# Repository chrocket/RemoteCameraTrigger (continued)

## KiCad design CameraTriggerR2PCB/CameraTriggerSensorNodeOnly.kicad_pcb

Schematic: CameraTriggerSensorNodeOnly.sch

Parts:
BZ1: Buzzer; Buzzer_TDK_PS1240P02BT_D12.2mm_H6.5mm
C1: 25uf; CP_Radial_Tantal_D5.0mm_P5.00mm
C2: 0.1uf; CP_Radial_Tantal_D5.0mm_P5.00mm
C3, C4, C5, C6: 0.01 μF; C_Disc_D7.5mm_W2.5mm_P5.00mm
D1: LED Arm; LED_D3.0mm
D2: LED Trig; LED_D3.0mm
D3: D; D_DO-201AD_P12.70mm_Horizontal
D4: PWR; LED_D3.0mm
GND1: TestPoint; TestPoint_Keystone_5000-5004_Miniature
H1, H2, H3, H4: MountingHole_3.7mm_Pad
IC1: 3178; Mouser2 Part Number 485-3178
J1: Power; AMASS_XT30U-F_1x02_P5.0mm_Vertical
J2: Qwiic_Connector; 1X04_1MM_RA_STRESSRELIEF
J3: Aux out; TerminalBlock_TE_282834-2_1x02_P2.54mm_Horizontal
J4: HighLowIn; TerminalBlock_TE_282834-3_1x03_P2.54mm_Horizontal
J5: Laser; TerminalBlock_TE_282834-2_1x02_P2.54mm_Horizontal
J6: Sensor; TerminalBlock_TE_282834-3_1x03_P2.54mm_Horizontal
J7: XLR5; Jack_XLR_Neutrik_NC5MBH_Horizontal
J13: Serial; TerminalBlock_TE_282834-4_1x04_P2.54mm_Horizontal
J14: Ext power switch; TerminalBlock_TE_282834-2_1x02_P2.54mm_Horizontal
Q1: PN2222A; TO-92L_HandSolder
Q2: KSC1815YTA; TO-92L_Inline_Wide
R1, R2, R5, R6: 1K; R_Axial_DIN0207_L6.3mm_D2.5mm_P7.62mm_Horizontal
R3: 5K; R_Axial_DIN0207_L6.3mm_D2.5mm_P7.62mm_Horizontal
R4: 220; R_Axial_DIN0207_L6.3mm_D2.5mm_P7.62mm_Horizontal
R8: 15K; R_Axial_DIN0207_L6.3mm_D2.5mm_P7.62mm_Horizontal
RV1: 1K; Potentiometer_Alps_RK09K_Single_Vertical
SW1: AS11CB; Manufacturer_Part_Number AS11CB; Mouser Part Number 633-AS11CB
SW2: SW_Arm; KSA_Tactile_SPST
SW3: SW_Poll; KSA_Tactile_SPST
SW4: SW_SPDT; SW_Slide_1P2T_CK_OS102011MS2Q
TP1: Gnd; TestPoint_Keystone_5000-5004_Miniature
TP1+5: +5V; TestPoint_Keystone_5010-5014_Multipurpose
TP2+3.3V1: +3.3V; TestPoint_Keystone_5010-5014_Multipurpose
TP3Arm1: Arm; TestPoint_Keystone_5010-5014_Multipurpose
TP4Fire1: Fire; TestPoint_Keystone_5010-5014_Multipurpose
TP7Poll1: Poll; TestPoint_Keystone_5010-5014_Multipurpose
TP8: HighLowIn; TestPoint_Keystone_5010-5014_Multipurpose
TP9: LowHighIn; TestPoint_Keystone_5010-5014_Multipurpose
U1: LM7805_TO220; TO-220-3_Vertical

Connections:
+3V3: BZ1.1 (-), C4.1, IC1.27, J2.2, J4.3, J6.1, J7.3, R6.1, RV1.1, TP2+3.3V1.1
+5V: C2.1, C3.1, IC1.3, J5.1, J7.1, J13.1, R4.1, TP1+5.1, U1.3 (VO); also elsewhere on the board
+7.5V: J1.2, J14.2, SW1.1
/13: IC1.4
/A0: IC1.24
/A4: IC1.20
/AREF: IC1.26
/EN: IC1.2
/FREE: IC1.13
/MISO: IC1.16
/MOSI: IC1.17
/SCK: IC1.18
/VBAT: IC1.1
/~RST: IC1.28
ArmIn: IC1.23, SW2.2
ArmInd: IC1.9, R1.2, TP3Arm1.1
AuxIn: C5.1, IC1.21, J4.2, SW4.1, TP8.1
AuxOut: IC1.8, R3.2
Buzzer: IC1.7, R2.2
GND: C1.2, C2.2, C3.2, C4.2, C5.2, C6.2, D4.1 (K), GND1.1, H1.1, H2.1, H3.1, H4.1, IC1.25, J1.1, J2.1, J3.2, J4.1, J6.3, J7.5, J13.4, Q1.1 (E), Q2.1, R5.1, R8.2, RV1.3, SW2.1, SW3.1, TP1.1, U1.2 (GND); also elsewhere on the board
Laser: J5.2, J7.2, Q1.3 (C)
unnamed: BZ1.2 (+), Q2.2, R6.2
unnamed: C1.1, D3.1 (K), U1.1 (VI)
unnamed: D1.1 (K), Q1.2 (B)
unnamed: D1.2 (A), R1.1
unnamed: D2.1 (K), R5.2
unnamed: D3.2 (A), J14.1, SW1.3
unnamed: D4.2 (A), R4.2
unnamed: J3.1, R3.1
unnamed: J7.4, SW4.2
unnamed: Q2.3, R2.1
Poll: IC1.22, SW3.2, TP7Poll1.1
Rx_serial: IC1.15, J13.2
SCL_qwiic: IC1.11, J2.4
SDA_qwiic: IC1.12, J2.3
SensorIn: C6.1, IC1.10, J6.2, R8.1, SW4.3, TP9.1
Shutter: D2.2 (A), IC1.5, TP4Fire1.1
Threshold: IC1.19, RV1.2
Tx_serial: IC1.14, J13.3

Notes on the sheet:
+3v
GND
+3.3V
RocketTrig Curtis Heisey

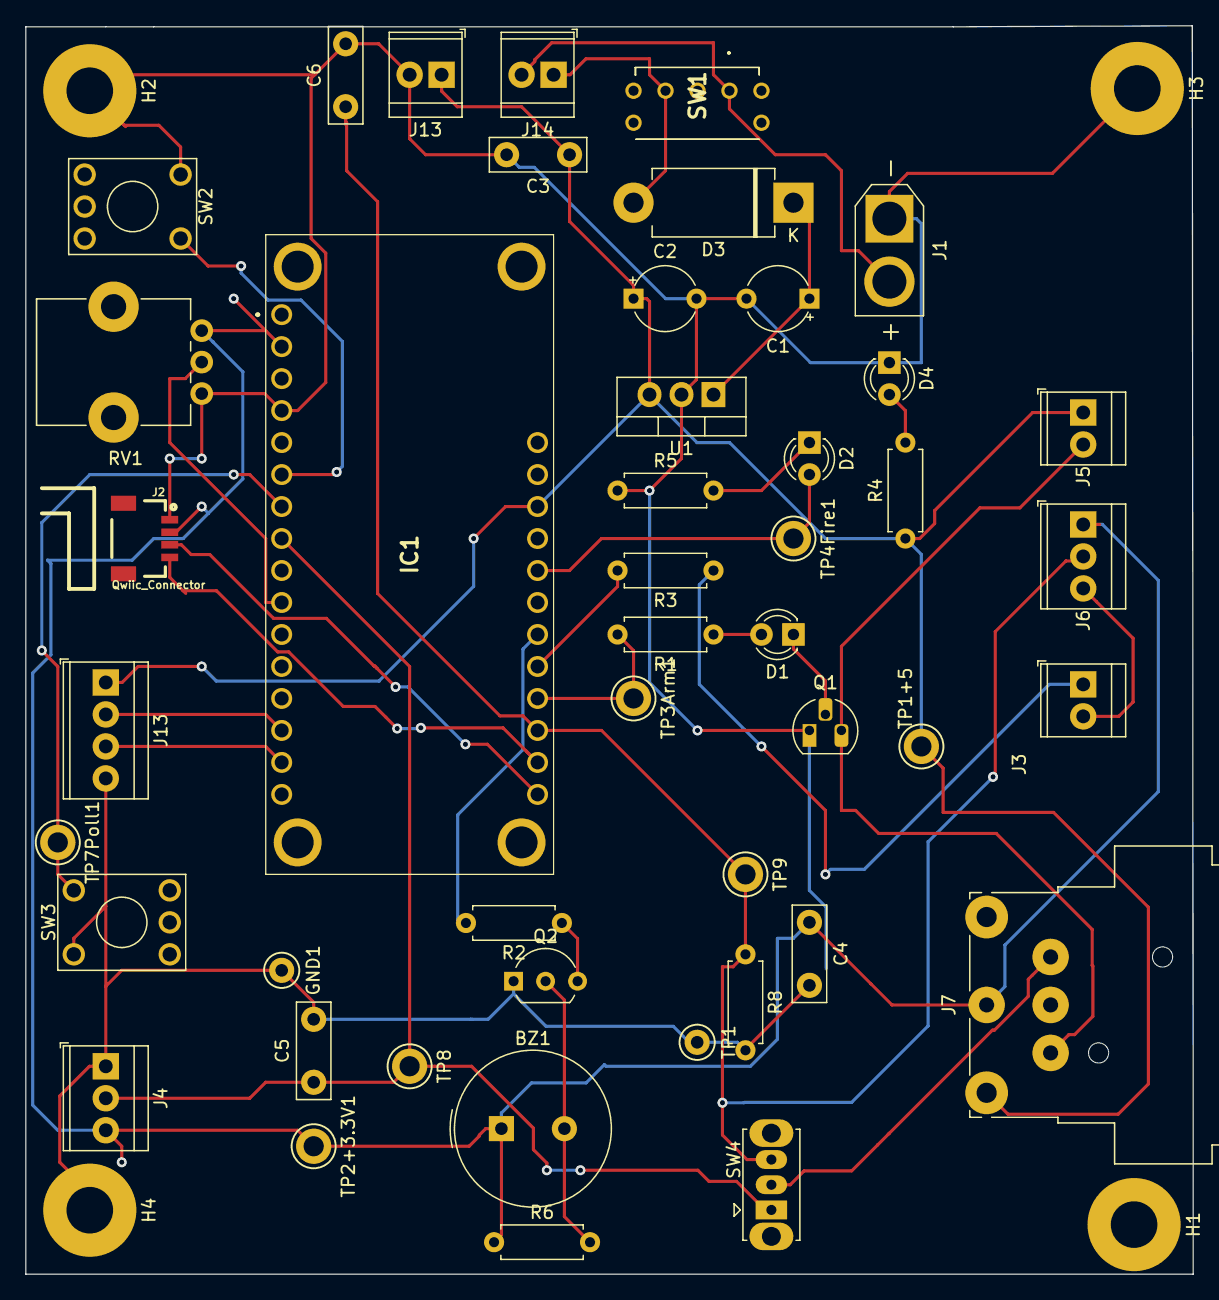
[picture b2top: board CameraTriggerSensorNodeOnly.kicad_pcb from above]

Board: 2 copper layers, 92.7 x 99.1 mm, 50 parts (0 on the bottom side), 28 nets.

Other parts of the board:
J13#2: +5V Always on; TerminalBlock_TE_282834-2_1x02_P2.54mm_Horizontal

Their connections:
+5V: J13#2.1; also elsewhere on the board
GND: J13#2.2; also elsewhere on the board

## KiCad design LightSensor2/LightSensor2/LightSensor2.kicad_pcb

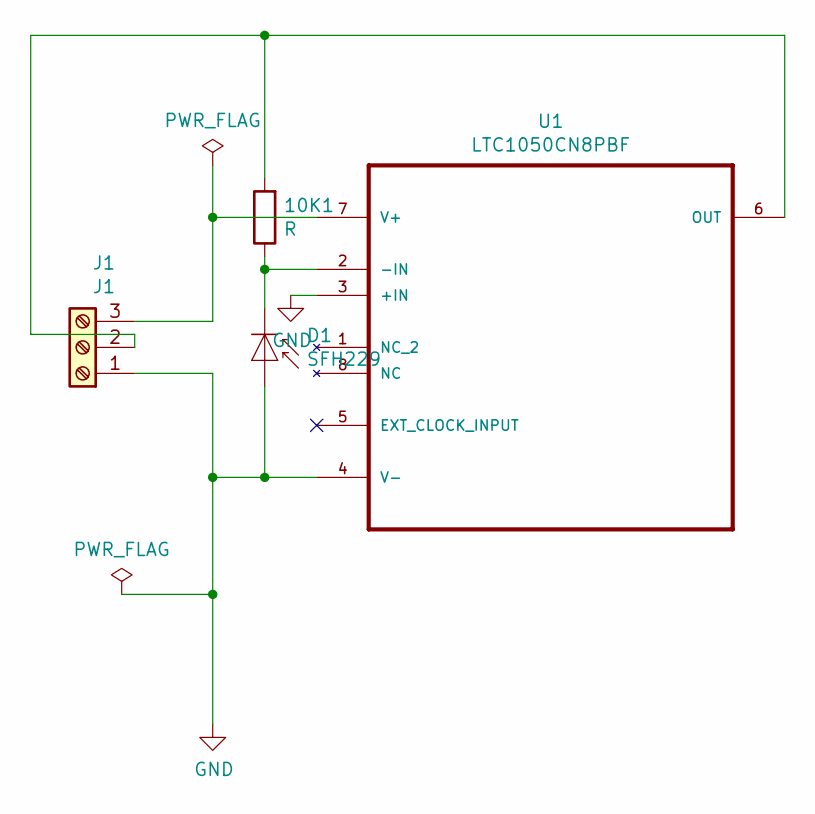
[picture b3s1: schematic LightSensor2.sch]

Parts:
10K1: R; R_Axial_DIN0207_L6.3mm_D2.5mm_P10.16mm_Horizontal
D1: SFH229; LED_D5.0mm_IRGrey
J1: J1; TerminalBlock_TE_282834-3_1x03_P2.54mm_Horizontal
U1: LTC1050CN8PBF; DIP-8_W7.62mm_LongPads

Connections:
GND: D1.2 (A), J1.1, U1.3 (+IN), U1.4 (V-)
unnamed: 10K1.1, D1.1 (K), U1.2 (-IN)
unnamed: 10K1.2, J1.2, U1.6 (OUT)
unnamed: J1.3, U1.7 (V+)

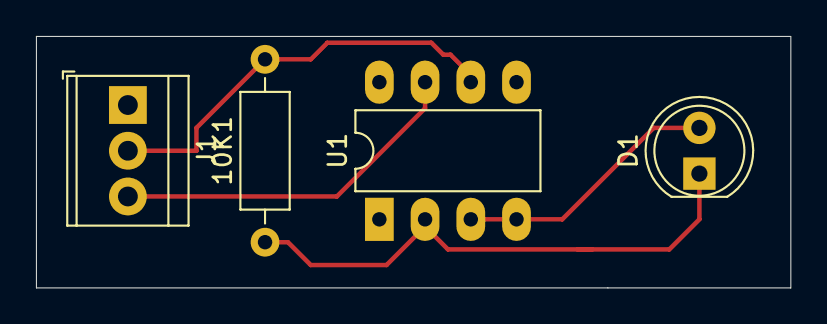
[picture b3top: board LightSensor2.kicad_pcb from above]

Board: 2 copper layers, 41.9 x 14.0 mm, 4 parts (0 on the bottom side), 4 nets.

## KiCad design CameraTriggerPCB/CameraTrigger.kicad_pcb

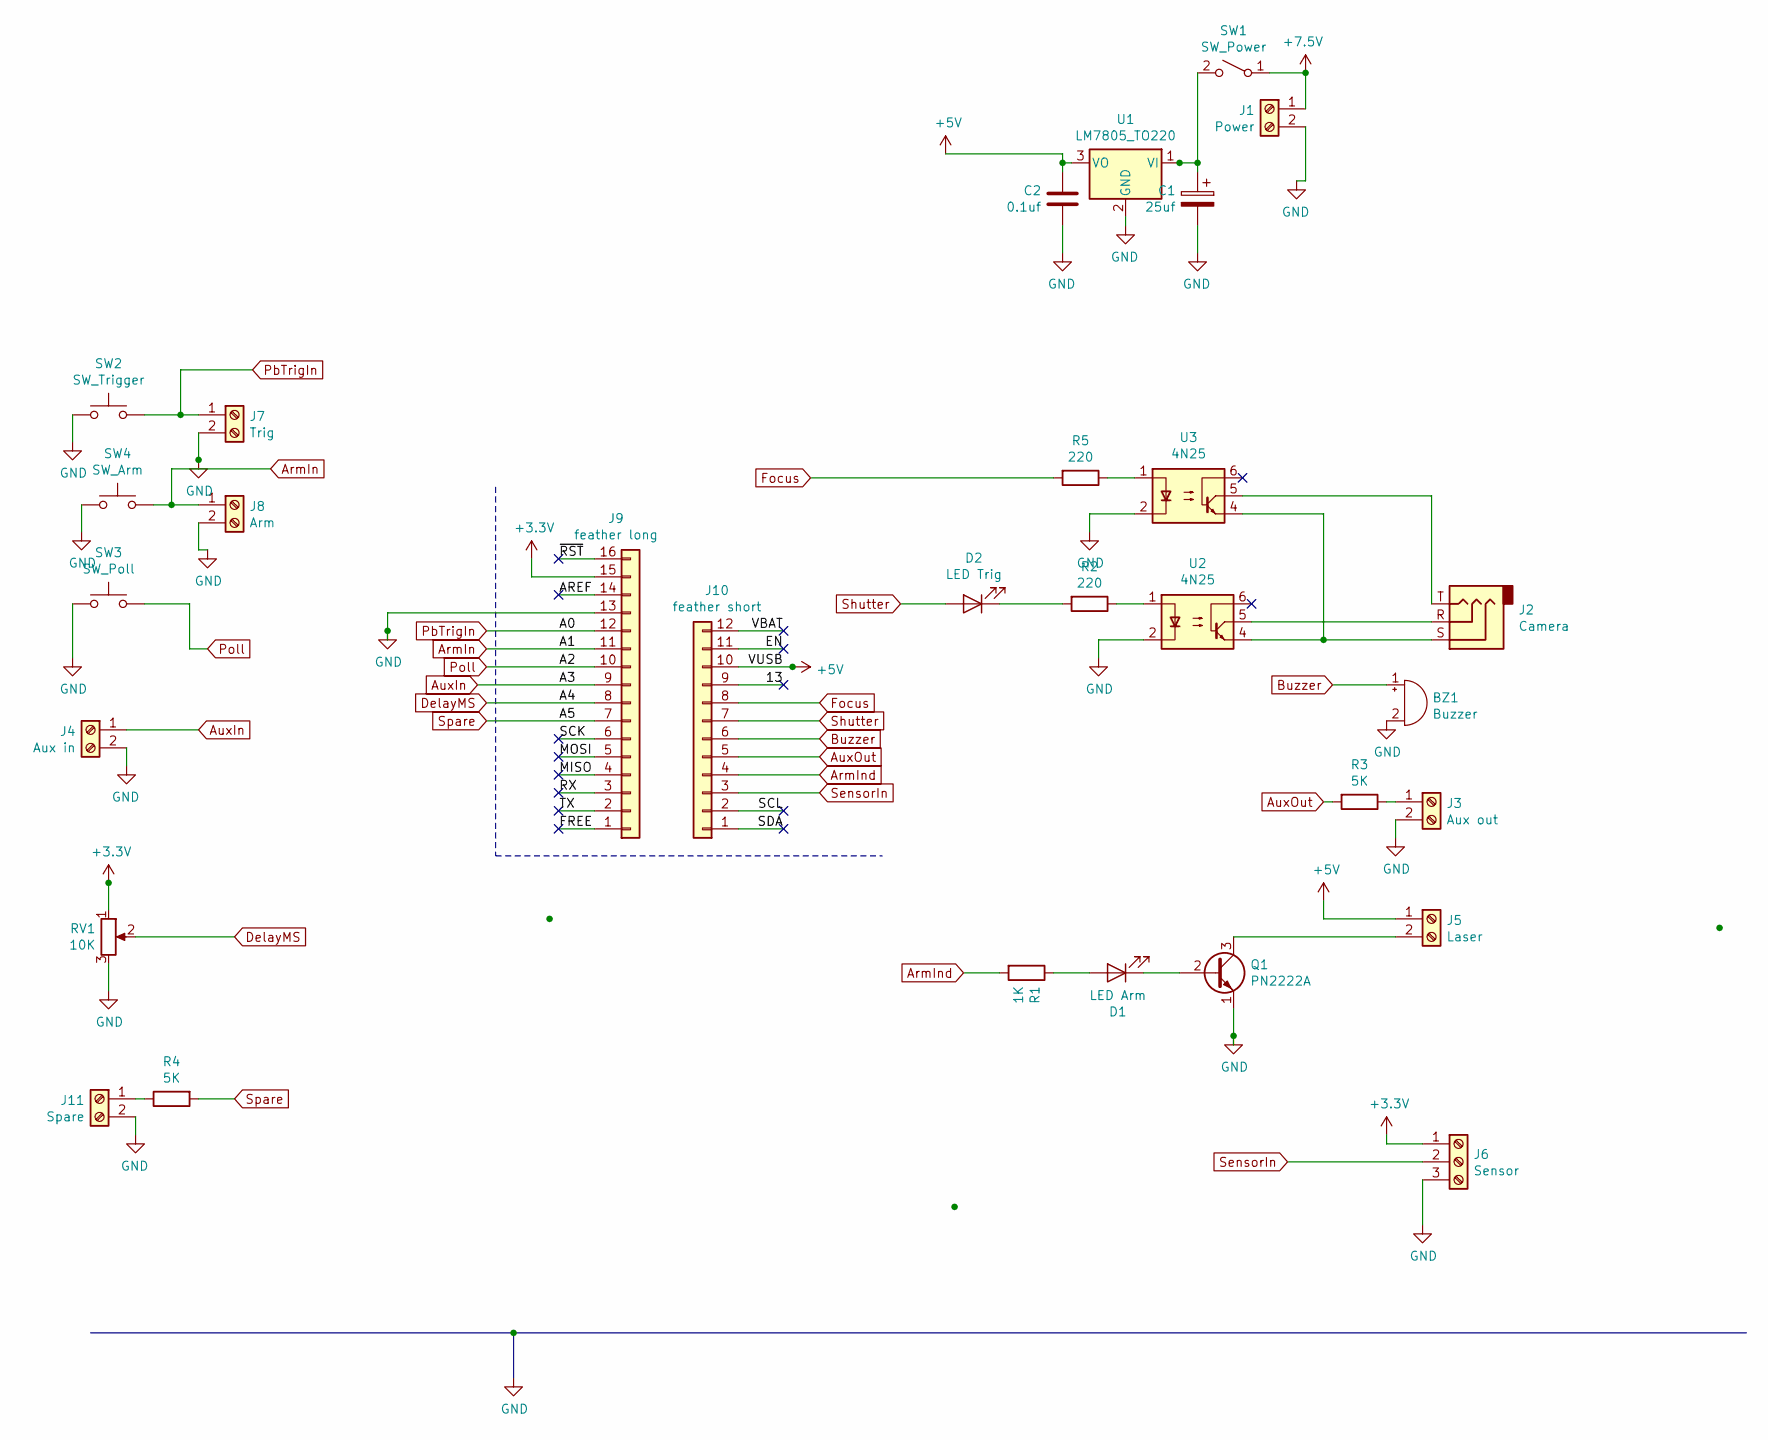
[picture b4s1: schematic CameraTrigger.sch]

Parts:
BZ1: Buzzer; Buzzer_TDK_PS1240P02BT_D12.2mm_H6.5mm
C1: 25uf; CP_Radial_Tantal_D5.0mm_P5.00mm
C2: 0.1uf; CP_Radial_Tantal_D5.0mm_P5.00mm
D1: LED Arm; LED_D2.0mm_W4.8mm_H2.5mm_FlatTop
D2: LED Trig; LED_D2.0mm_W4.8mm_H2.5mm_FlatTop
J1: Power; TerminalBlock_TE_282834-2_1x02_P2.54mm_Horizontal
J2: Camera; Jack_3.5mm_CUI_SJ1-3533NG_Horizontal_CircularHoles
J3: Aux out; TerminalBlock_TE_282834-2_1x02_P2.54mm_Horizontal
J4: Aux in; TerminalBlock_TE_282834-2_1x02_P2.54mm_Horizontal
J5: Laser; TerminalBlock_TE_282834-2_1x02_P2.54mm_Horizontal
J6: Sensor; TerminalBlock_TE_282834-3_1x03_P2.54mm_Horizontal
J7: Trig; TerminalBlock_TE_282834-2_1x02_P2.54mm_Horizontal
J8: Arm; TerminalBlock_TE_282834-2_1x02_P2.54mm_Horizontal
J9: feather long; PinHeader_1x16_P2.54mm_Vertical
J10: feather short; PinHeader_1x12_P2.54mm_Vertical
J11: Spare; TerminalBlock_TE_282834-2_1x02_P2.54mm_Horizontal
Q1: PN2222A; TO-92_Inline
R1: 1K; R_Axial_DIN0207_L6.3mm_D2.5mm_P7.62mm_Horizontal
R2, R5: 220; R_Axial_DIN0207_L6.3mm_D2.5mm_P7.62mm_Horizontal
R3, R4: 5K; R_Axial_DIN0207_L6.3mm_D2.5mm_P7.62mm_Horizontal
RV1: 10K; Potentiometer_Alps_RK09K_Single_Vertical
SW1: SW_Power; SW_DIP_SPSTx01_Slide_9.78x4.72mm_W7.62mm_P2.54mm
SW2: SW_Trigger; KSA_Tactile_SPST
SW3: SW_Poll; KSA_Tactile_SPST
SW4: SW_Arm; KSA_Tactile_SPST
U1: LM7805_TO220; TO-220-3_Vertical
U2, U3: 4N25; DIP-6_W7.62mm

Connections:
+3V3: J6.1, J9.15, RV1.1
+5V: C2.1, J5.1, J10.10, U1.3 (VO)
+7.5V: J1.1, SW1.1 (A)
/13: J10.9
/AREF: J9.14
/EN: J10.11
/FREE: J9.1
/MISO: J9.4
/MOSI: J9.5
/RX: J9.3
/SCK: J9.6
/SCL: J10.2
/SDA: J10.1
/TX: J9.2
/VBAT: J10.12
/~RST: J9.16
ArmIn: J8.1, J9.11, SW4.2
ArmInd: J10.4, R1.2
AuxIn: J4.1, J9.9
AuxOut: J10.5, R3.2
Buzzer: BZ1.1 (-), J10.6
DelayMS: J9.8, RV1.2
Focus: J10.8, R5.2
GND: BZ1.2 (+), C1.2, C2.2, J1.2, J3.2, J4.2, J6.3, J7.2, J8.2, J9.13, J11.2, Q1.1 (E), RV1.3, SW2.1, SW3.1, SW4.1, U1.2 (GND), U2.2, U3.2
unnamed: C1.1, SW1.2 (B), U1.1 (VI)
unnamed: D1.1 (K), Q1.2 (B)
unnamed: D1.2 (A), R1.1
unnamed: D2.1 (K), R2.2
unnamed: J2.R, U2.5
unnamed: J2.S, U2.4, U3.4
unnamed: J2.T, U3.5
unnamed: J3.1, R3.1
unnamed: J5.2, Q1.3 (C)
unnamed: J11.1, R4.1
unnamed: R2.1, U2.1
unnamed: R5.1, U3.1
PbTrigIn: J7.1, J9.12, SW2.2
Poll: J9.10, SW3.2
SensorIn: J6.2, J10.3
Shutter: D2.2 (A), J10.7
Spare: J9.7, R4.2

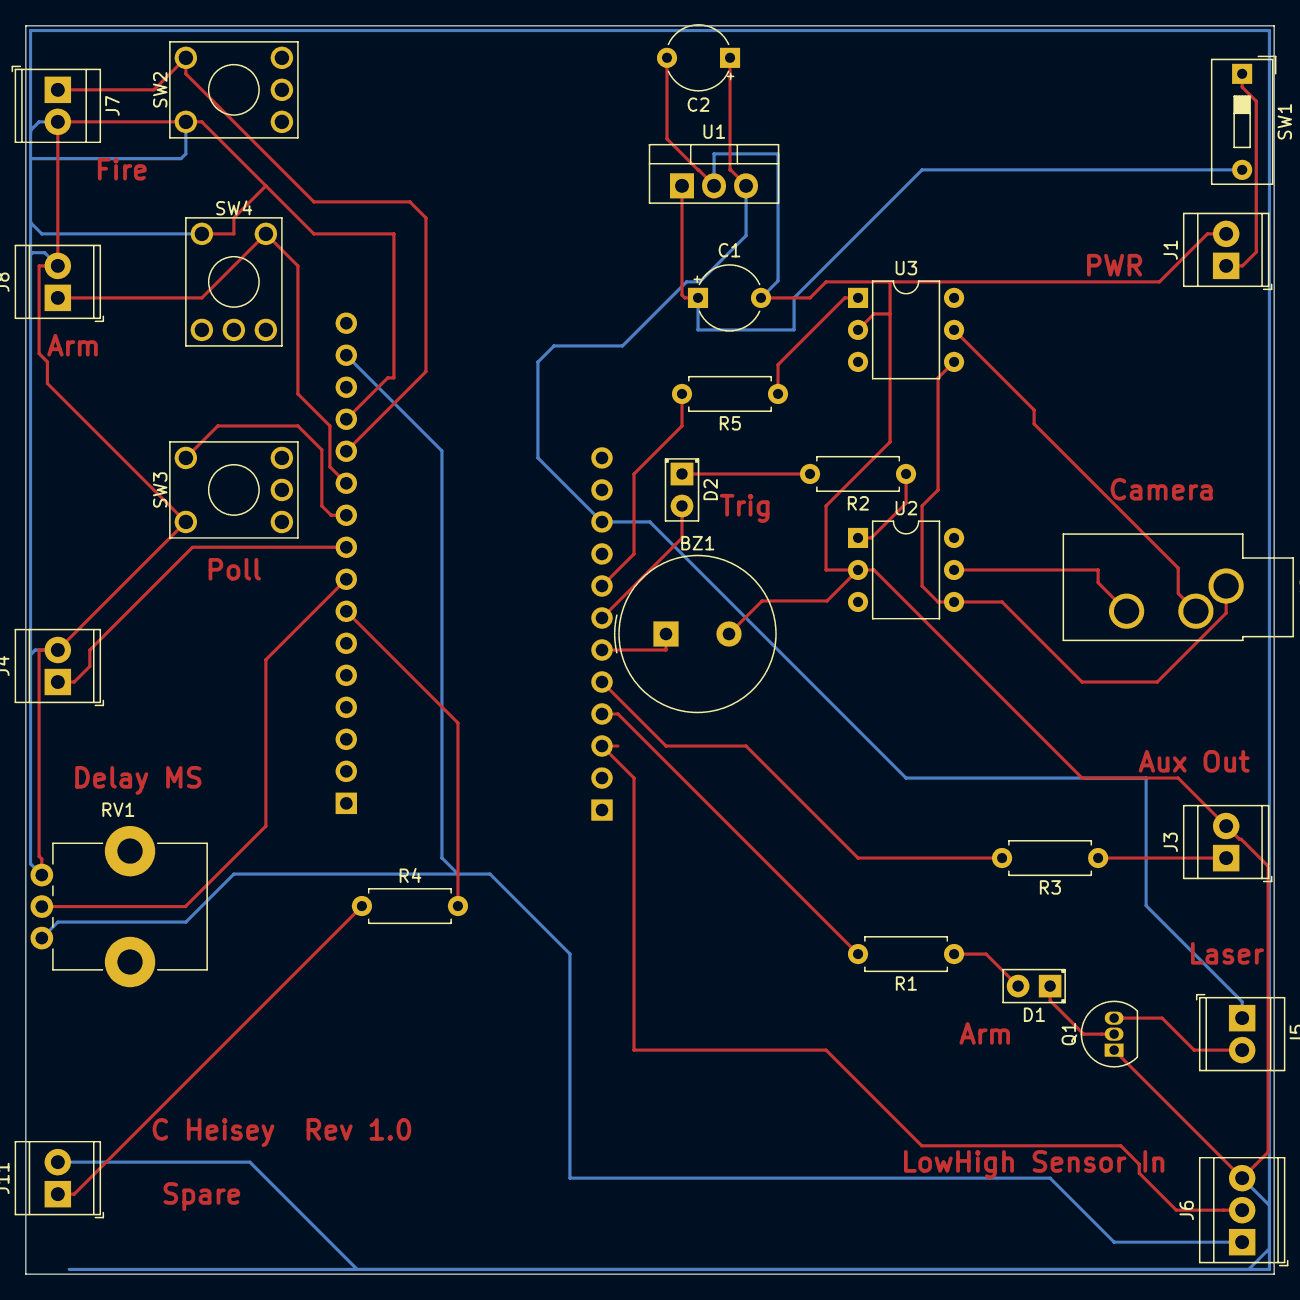
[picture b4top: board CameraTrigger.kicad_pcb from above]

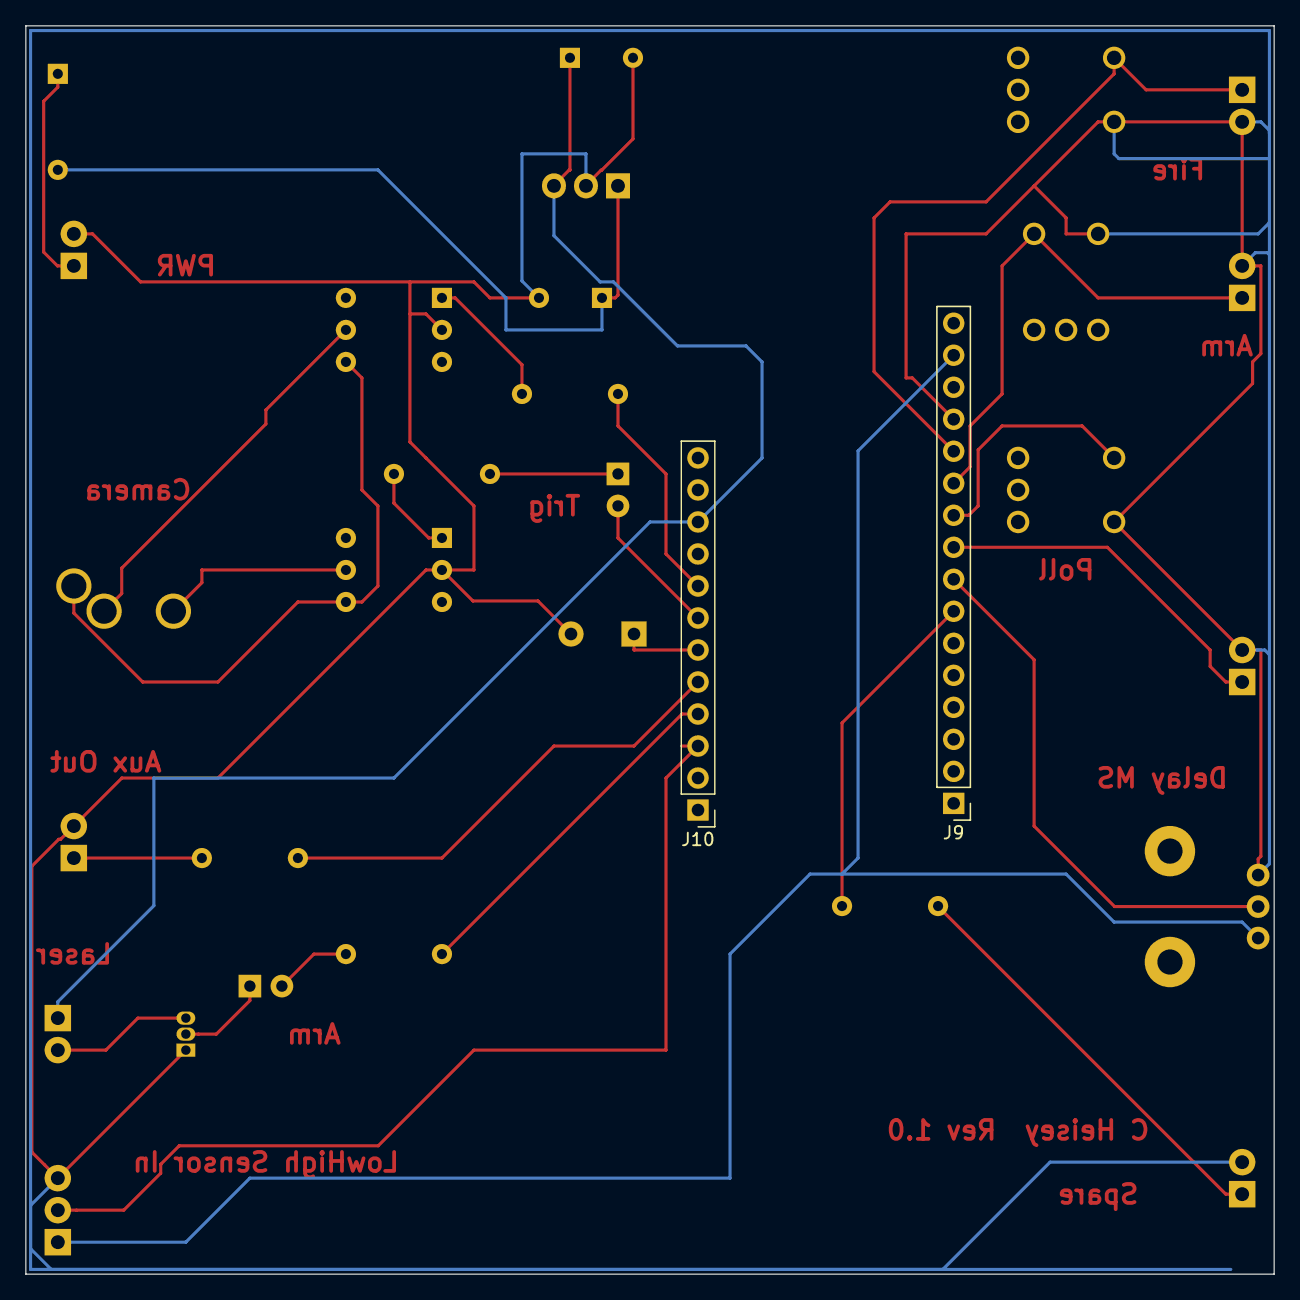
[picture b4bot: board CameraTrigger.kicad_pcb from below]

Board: 2 copper layers, 99.1 x 99.1 mm, 30 parts (2 on the bottom side), 28 nets.

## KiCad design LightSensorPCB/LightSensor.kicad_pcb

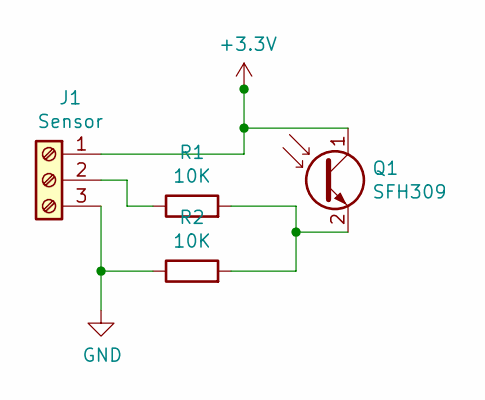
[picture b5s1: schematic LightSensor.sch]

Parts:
J1: Sensor; TerminalBlock_TE_282834-3_1x03_P2.54mm_Horizontal
Q1: SFH309; LED_D3.0mm_Clear
R1, R2: 10K; R_Axial_DIN0207_L6.3mm_D2.5mm_P7.62mm_Horizontal

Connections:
+3V3: J1.1, Q1.1 (C)
GND: J1.3, R2.1
unnamed: J1.2, R1.1
unnamed: Q1.2 (E), R1.2, R2.2

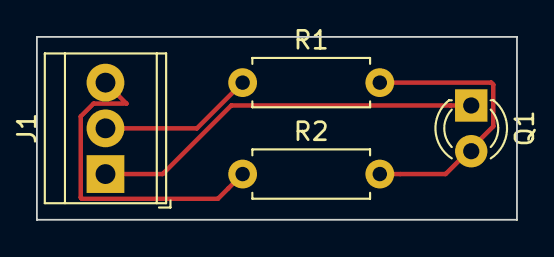
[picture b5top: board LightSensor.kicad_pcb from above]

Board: 2 copper layers, 26.7 x 10.2 mm, 4 parts (0 on the bottom side), 4 nets.

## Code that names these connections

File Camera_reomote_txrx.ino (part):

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const unsigned int HIGHLOW_TRIGGER_IN_PIN=17;  // If armed, High to low transition will trigger
const unsigned int PUSH_IN_PIN=14; // Push button trigger override ("arm" does not have to be set)
const unsigned int ARM_IN_PIN=15;  // Push button to arm sensor
const unsigned int POLLREQUEST_IN_PIN=16;  // Push button to send roll call poll request to other nodes
const unsigned int DELAYMS_PIN=18;  // Pot on analog in to set delay 0-200 ms
const unsigned int SPARE_PIN=19;  // Reserved for future use

// outputs
// LED_OUT 13
const unsigned int BUZZER_OUT_PIN= 10;            // Pin to audible indicator
const unsigned int CAMERA_TRIGGER_OUT_PIN = 12;   // Pin for focus opto-isolator
const unsigned int CAMERA_FOCUS_OUT_PIN = 11;     // Pin for shtter opto-isoloatr
const unsigned int AUX_OUT_PIN = 9;               // Pin for 2nd trigger output
const unsigned int ARM_INDICATOR_OUT_PIN = 6;     // Indicates sensor is armed, turns laser on

const unsigned int  ON_TIME_MS = 2000 ;          // Camera bulb on time when trigger fires (typical vals 1-3 seconds)      
const unsigned int  SHORT_TIME_MS = 200;
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  pinMode(POLLREQUEST_IN_PIN, INPUT_PULLUP);
  pinMode(ARM_IN_PIN, INPUT_PULLUP);
  pinMode(PUSH_IN_PIN, INPUT_PULLUP); 
  pinMode(DELAYMS_PIN, INPUT);
  pinMode(SPARE_PIN, INPUT_PULLUP);

  

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    cameraTriggerTimerShort.check();

    // Read delay pot value
    int delayms = analogRead(DELAYMS_PIN);

   // TRIGGER OVERRIDE PB
   // If user presses "fire" push button, it will trigger outputs
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
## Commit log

2019-08-20 Basic working SF-30B Lidar with LCD and camera trigger
2019-08-20 unit test codes
2019-08-23 Changed freq to 915.3
2019-08-23 Updated freq to 915.3
2019-09-08 Attached the RF link
    Attached the RF link to Adafruit M0 Feather on output pin 5
2019-09-08 Voltage divider read
2019-09-08 Camera_remote_tx/rx
    RF lin camera trigger
    RadioHead69_AddrDemo_TX_redboard.ino tried to hook RFM69 directly to redboard, but didn't work
2019-09-08 More UT stuff
2019-12-15 Add files via upload
    Added timer so can only press button every 0.1 sec
2019-12-17 Add files via upload
    Adding Adafruit M0 Packet Radio Board docs
2019-12-23 Add files via upload
    Program to get unique board id for Feather M0
2019-12-23 Add files via upload
    My unique id 3 chars
2019-12-25 Add files via upload
    PCB stuff
2019-12-25 Add files via upload
    Updated pinout to PCB
2019-12-25 Add files via upload
    Updated pinout
2019-12-26 Add files via upload
    If any trigger goes off, isArmed is set to false.
2020-01-04 Add files via upload
    Updated BOM to fix a few hole placements
2020-01-04 Add files via upload
    Added Adafruit 3176 Packet radio to BOM
    Added 2.5 mm 3-position camera jack as alternative to J2
2020-01-04 Add files via upload
    Switching pins 10,11
2020-01-06 Add files via upload
    Rev2 board
2020-01-19 Add files via upload
    Fixes on R2 board
2020-01-23 Rev2B changes
2020-01-27 Rev2B
2020-01-29 Rev2B Final
2020-01-29 Moved jacks closer to board edge
2020-02-27 Add files via upload
    Made poll click the camera, briefly.
    Send trigger message out twice after a sensor goes off
2020-03-07 Add files via upload
    Final build before switching over to LoRa
2020-03-08 Add files via upload
    Version for RFM69/RFM95 works for RFM69 (Use #define to select which one)
2020-03-08 Add files via upload
    Unommenting serial monitor debugging
2020-03-08 Add files via upload
    Support for RFM95
2020-03-12 Add files via upload
    Updated BOM with mounting hardware
2020-03-15 Unit test codes for zio ultrasound detector, distance sensor, and oled display
2020-03-16 Add files via upload
    Added latency output
2020-03-19 Add files via upload
    Increasing "on" time to 2 sec
2020-03-19 Delete Camera_reomote_txrx.ino
    Oops file in wrong place
2020-04-11 Add files via upload
    Fixing bug so that trigger override fires camera right away
2020-04-17 Add files via upload
    Sensor node only
2020-04-20 Add files via upload
    Adding LightSensor2
2020-04-20 Add files via upload
    LightSensor2 (Alex) and BreakWire schematic
2020-04-26 Add files via upload
    Rdo SCK SDL to correct pins
2020-04-28 Add files via upload
    Adding Arm switch back in
    Adding transistor driver on buzzer
2020-05-13 Add files via upload
    Broke schematic into hierarchical sheets
2020-05-13 Update README.md
    Updating Readme
2020-05-14 Add files via upload
    First cut at modules
2020-05-18 Add files via upload
    Changes from 5/17 Zoom sensor
2020-05-23 Add files via upload
    Updates from last few sessions
2020-05-29 Add files via upload
    Adding XLR connector
2020-05-29 Add files via upload
    Added XLR connector
2020-05-31 Add files via upload
    Production version
2020-06-02 Add files via upload
    Added comment to schematic for XLR connector (male).
2020-12-24 Add files via upload
    JCBPCB Assembly
2020-12-24 Add files via upload
    Rotated D7
2020-12-25 Add files via upload
    Sensor node only is working
